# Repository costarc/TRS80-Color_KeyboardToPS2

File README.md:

# TRS80-Color_KeyboardToPS2
Adapter to convert CoCo matrix keyboard to PS/2

This is w working in progress - not tested as of 09/11/2023.
The PIC controller software has not been developed yet as well, so for now its useless unless you develop the softwre yourself.

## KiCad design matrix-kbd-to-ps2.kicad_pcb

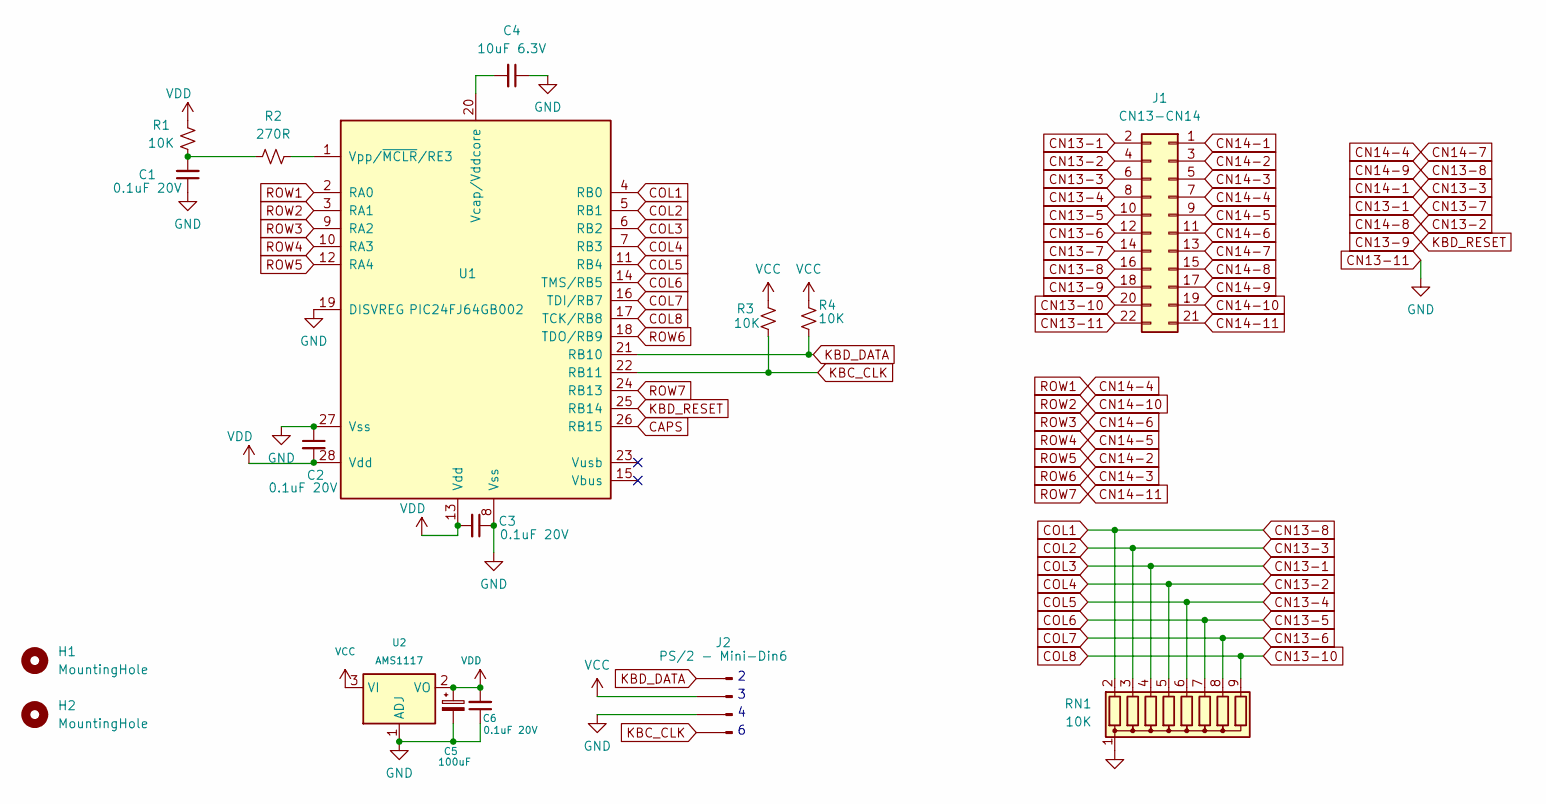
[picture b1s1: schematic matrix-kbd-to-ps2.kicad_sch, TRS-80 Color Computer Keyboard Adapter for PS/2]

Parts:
C1, C2, C3, C6: 0.1uF 20V; C_Disc_D3.0mm_W1.6mm_P2.50mm
C4: 10uF 6.3V; C_Disc_D3.0mm_W1.6mm_P2.50mm
C5: 100uF; CP_Radial_D5.0mm_P2.50mm
H1, H2: MountingHole; MountingHole_2.5mm
J1: CN13-CN14; PinSocket_2x11_P2.54mm_Horizontal
J2: PS/2 - Mini-Din6; PinHeader_1x04_P2.54mm_Vertical
R1, R3, R4: 10K; R_Axial_DIN0207_L6.3mm_D2.5mm_P7.62mm_Horizontal
R2: 270R; R_Axial_DIN0207_L6.3mm_D2.5mm_P7.62mm_Horizontal
RN1: 10K; R_Array_SIP9
U1: PIC24FJ64GB002; DIP-28_W7.62mm
U2: AMS1117; SOT-223-3_TabPin2

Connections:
CAPS: U1.26 (RB15)
CN13-1: J1.2, J1.14, RN1.4 (R3), U1.6 (RB2)
CN13-2: J1.4, J1.15, RN1.5 (R4), U1.7 (RB3)
CN13-3: J1.1, J1.6, RN1.3 (R2), U1.5 (RB1)
CN13-4: J1.8, RN1.6 (R5), U1.11 (RB4)
CN13-5: J1.10, RN1.7 (R6), U1.14 (TMS/RB5)
CN13-6: J1.12, RN1.8 (R7), U1.16 (TDI/RB7)
CN13-8: J1.16, J1.17, RN1.2 (R1), U1.4 (RB0)
CN13-9: J1.18, U1.25 (RB14)
CN13-10: J1.20, RN1.9 (R8), U1.17 (TCK/RB8)
CN13-11: C1.1, C2.1, C3.1, C4.1, C5.2, C6.1, J1.22, J2.3, RN1.1 (common), U1.8 (Vss), U1.19 (DISVREG), U1.27 (Vss), U2.1 (ADJ)
CN14-2: J1.3, U1.12 (RA4)
CN14-3: J1.5, U1.18 (TDO/RB9)
CN14-4: J1.7, J1.13, U1.2 (RA0)
CN14-5: J1.9, U1.10 (RA3)
CN14-6: J1.11, U1.9 (RA2)
CN14-10: J1.19, U1.3 (RA1)
CN14-11: J1.21, U1.24 (RB13)
KBC_CLK: J2.4, R3.2, U1.22 (RB11)
KBD_DATA: J2.1, R4.2, U1.21 (RB10)
unnamed: C1.2, R1.2, R2.2
unnamed: C4.2, U1.20 (Vcap/Vddcore)
unnamed: R2.1, U1.1 (Vpp/~MCLR/RE3)
VCC: J2.2, R3.1, R4.1, U2.3 (VI)
VDD: C2.2, C3.2, C5.1, C6.2, R1.1, U1.13 (Vdd), U1.28 (Vdd), U2.2 (VO)

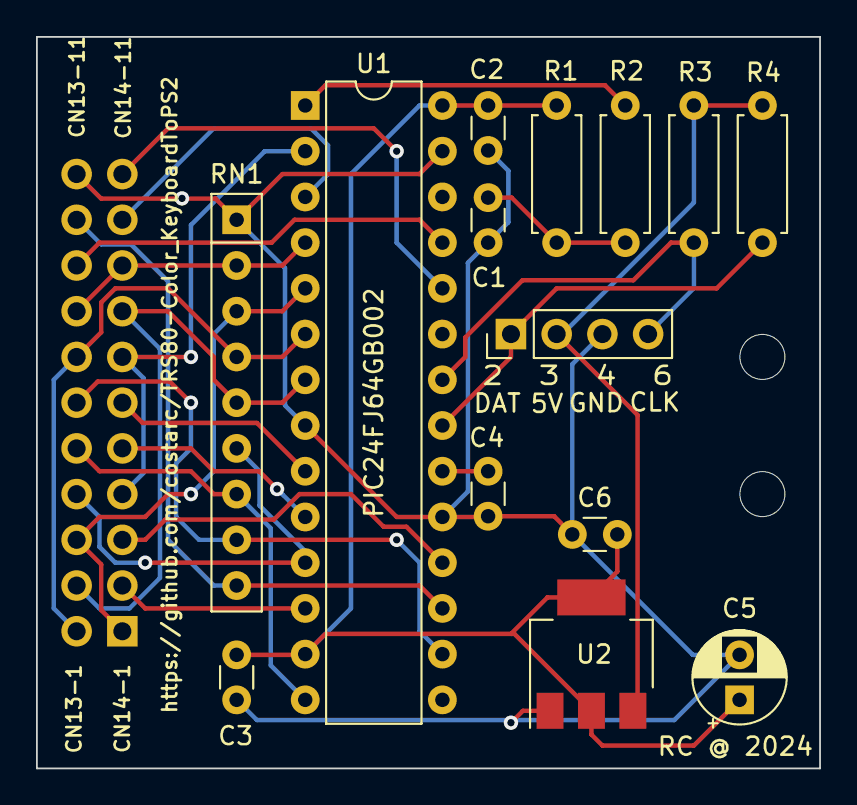
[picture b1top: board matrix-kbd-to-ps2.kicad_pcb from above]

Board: 2 copper layers, 43.5 x 40.6 mm, 17 parts (1 on the bottom side), 24 nets.

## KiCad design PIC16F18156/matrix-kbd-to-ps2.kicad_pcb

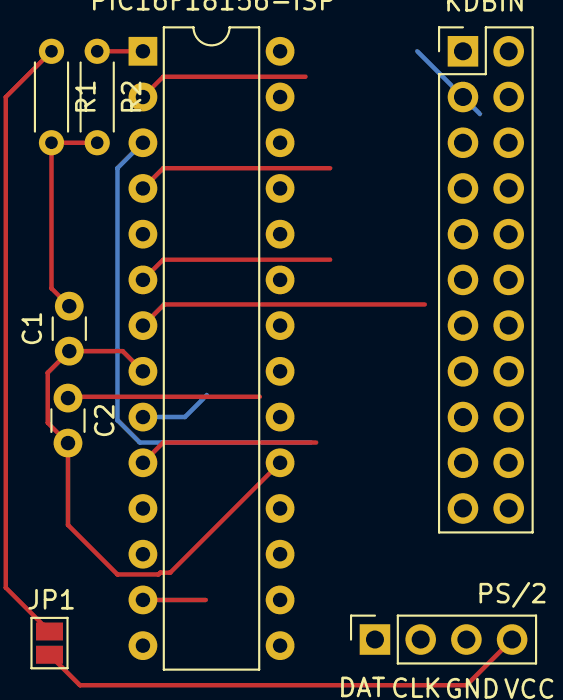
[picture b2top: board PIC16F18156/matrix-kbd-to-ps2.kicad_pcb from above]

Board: 2 copper layers, 8 parts (0 on the bottom side), 22 nets.

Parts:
C1: 10nF 16V; C_Disc_D3.0mm_W1.6mm_P2.50mm
C2: 0.1uF 16V; C_Disc_D3.0mm_W1.6mm_P2.50mm
J1: KDBIN; PinHeader_2x11_P2.54mm_Vertical
J2: PS/2; PinSocket_1x04_P2.54mm_Vertical
JP1: SolderJumper-2_P1.3mm_Open_Pad1.0x1.5mm
R1: 10K; R_Axial_DIN0204_L3.6mm_D1.6mm_P5.08mm_Horizontal
R2: 270R; R_Axial_DIN0204_L3.6mm_D1.6mm_P5.08mm_Horizontal
U1: PIC16F18156-ISP; DIP-28_W7.62mm

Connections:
CN13-1: J1.1, J1.13, U1.14 (RC3)
CN13-2: J1.3, J1.16, U1.10 (RA6)
CN13-3: J1.2, J1.5, U1.15 (RC4)
CN13-4: J1.7, U1.9 (RA7)
CN13-5: J1.9, U1.11 (RC0)
CN13-6: J1.11, U1.12 (RC1)
CN13-8: J1.15, J1.18, U1.16 (RC5)
CN13-10: J1.19, U1.13 (RC2)
CN14-2: J1.4, U1.17 (RC6)
CN14-3: J1.6, U1.2 (RA0)
CN14-4: J1.8, J1.14, U1.4 (RA2)
CN14-5: J1.10, U1.7 (RA5)
CN14-6: J1.12, U1.6 (RA4)
CN14-10: J1.20, U1.5 (RA3)
CN14-11: J1.22, U1.3 (RA1)
KBD_DATA: J2.1, U1.22 (RB1)
unnamed: C1.2, R1.2, R2.2
unnamed: J2.4, JP1.2 (B)
unnamed: C2.1, U1.20 (Vdd)
unnamed: R2.1, U1.1 (~MCLR/Vpp/RE3)
VDD: JP1.1 (A), R1.1
VSS: C1.1, C2.2, J2.3, U1.8 (Vss), U1.19 (Vss)

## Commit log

2023-11-09 rev0
2023-11-26 Added readme / revisions notes
2023-11-27 Revision 1
